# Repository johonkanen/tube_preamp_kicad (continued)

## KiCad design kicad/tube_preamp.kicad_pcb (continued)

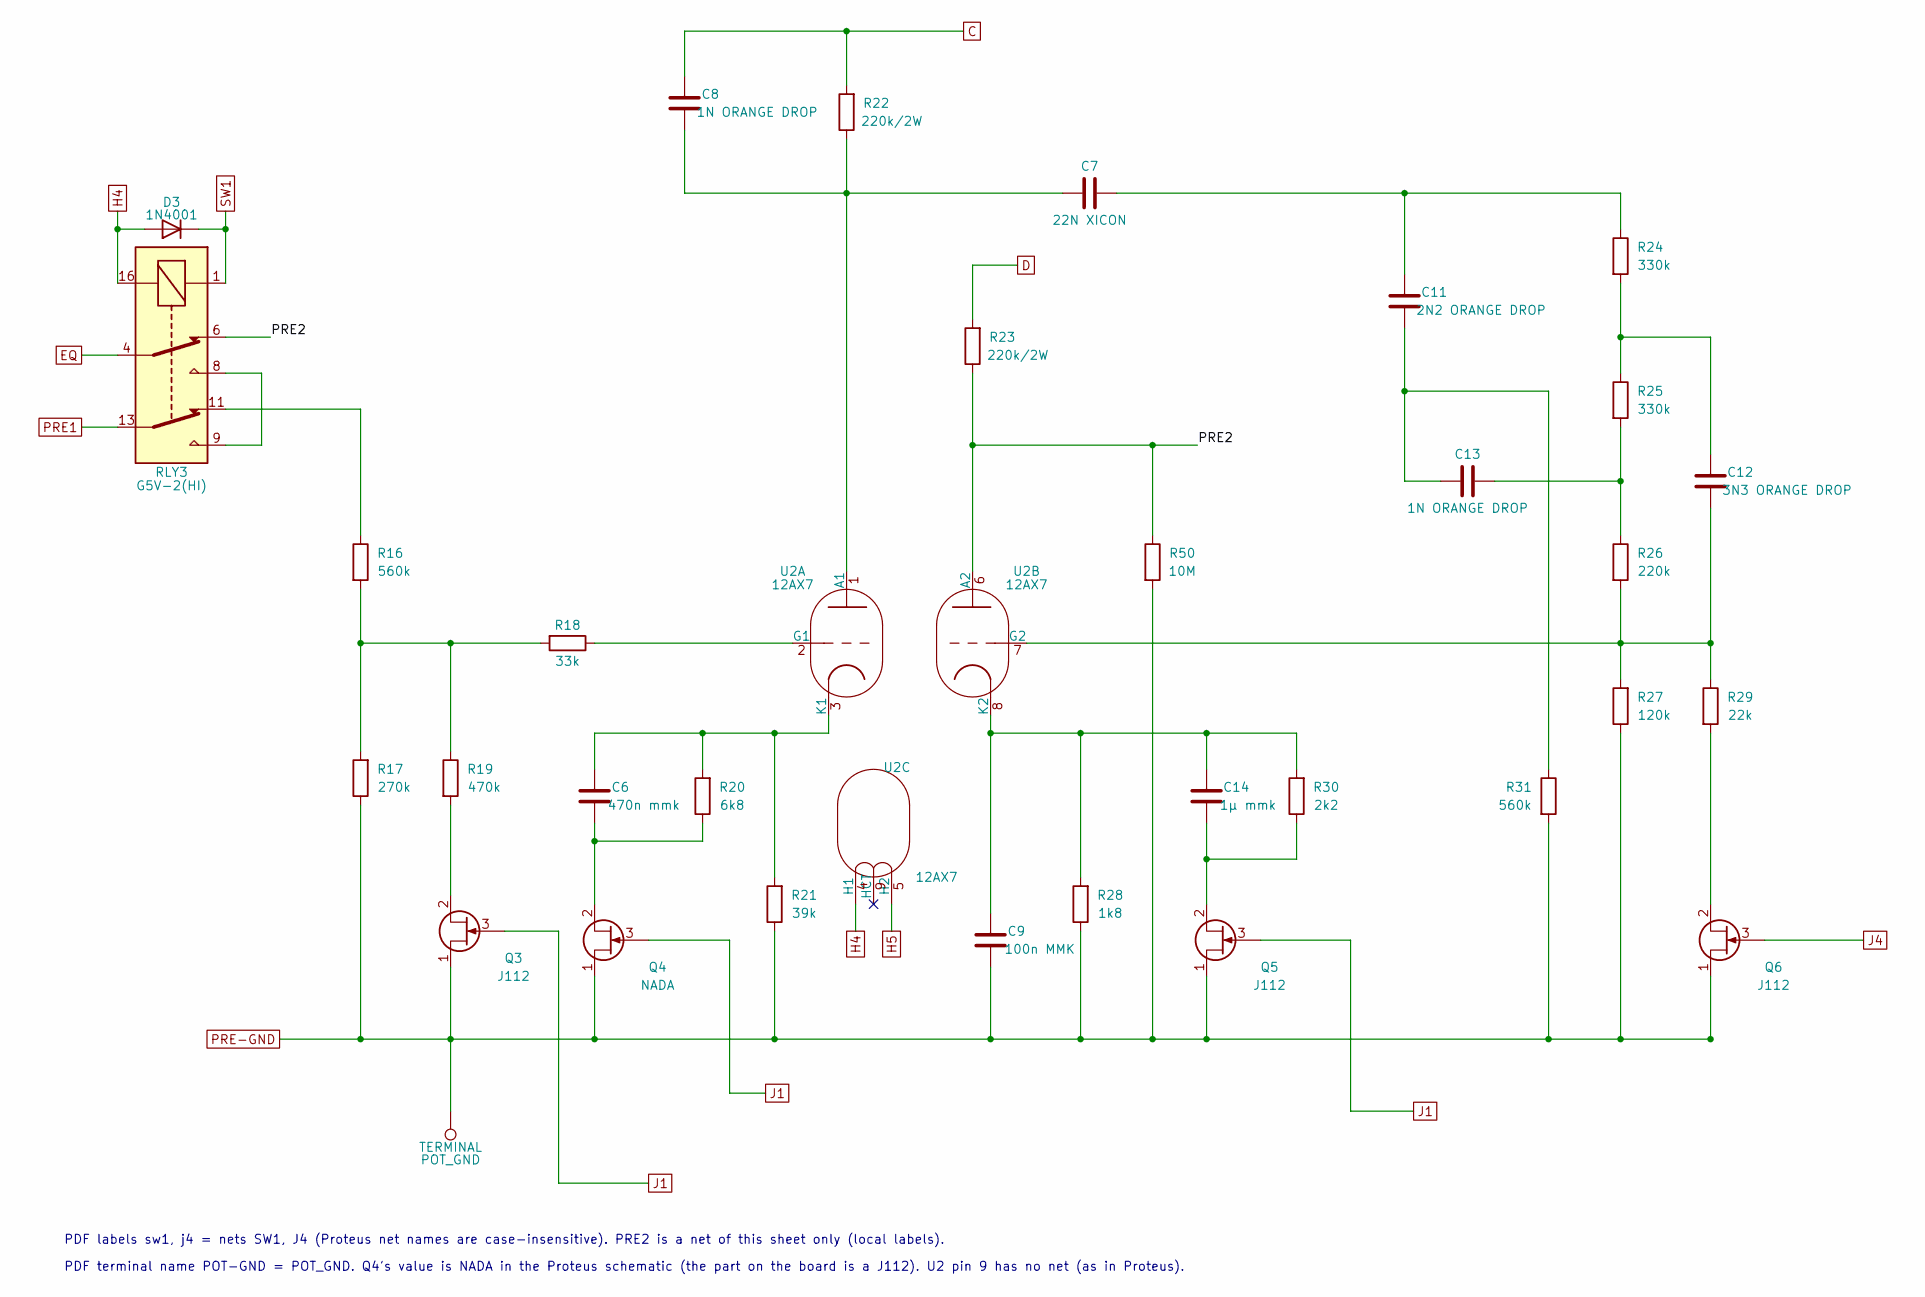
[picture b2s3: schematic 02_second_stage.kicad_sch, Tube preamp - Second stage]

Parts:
C6: 470n mmk; C_Rect_L7.2mm_W2.5mm_P5.00mm_FKS2_FKP2_MKS2_MKP2
C7: 22N XICON; C_Rect_L13.0mm_W6.0mm_P9.70mm
C8, C13: 1N ORANGE DROP; C_Rect_L16.5mm_W7.0mm_P9.70mm
C9: 100n MMK; C_Rect_L7.2mm_W2.5mm_P5.00mm_FKS2_FKP2_MKS2_MKP2
C11: 2N2 ORANGE DROP; C_Rect_L16.5mm_W7.0mm_P9.70mm
C12: 3N3 ORANGE DROP; C_Rect_L16.5mm_W7.0mm_P9.70mm
C14: 1µ mmk; C_Rect_L7.2mm_W5.0mm_P5.00mm
D3: 1N4001; D_DO-41_SOD81_P10.16mm_Horizontal_AK
POT_GND: TERMINAL; FlyLead_Pad_D3.048mm_Drill1.524mm
Q3, Q5, Q6: J112; TO-92_Inline_P2.03mm
Q4: NADA; TO-92_Inline_P2.03mm
R16, R31: 560k; R_Axial_DIN0207_L6.3mm_D2.5mm_P10.16mm_Horizontal
R17: 270k; R_Axial_DIN0207_L6.3mm_D2.5mm_P10.16mm_Horizontal
R18: 33k; R_Axial_DIN0207_L6.3mm_D2.5mm_P10.16mm_Horizontal
R19: 470k; R_Axial_DIN0207_L6.3mm_D2.5mm_P10.16mm_Horizontal
R20: 6k8; R_Axial_DIN0207_L6.3mm_D2.5mm_P10.16mm_Horizontal
R21: 39k; R_Axial_DIN0207_L6.3mm_D2.5mm_P10.16mm_Horizontal
R22, R23: 220k/2W; R_Axial_DIN0414_L11.9mm_D4.5mm_P19.05mm_Horizontal
R24, R25: 330k; R_Axial_DIN0207_L6.3mm_D2.5mm_P10.16mm_Horizontal
R26: 220k; R_Axial_DIN0207_L6.3mm_D2.5mm_P10.16mm_Horizontal
R27: 120k; R_Axial_DIN0207_L6.3mm_D2.5mm_P10.16mm_Horizontal
R28: 1k8; R_Axial_DIN0207_L6.3mm_D2.5mm_P10.16mm_Horizontal
R29: 22k; R_Axial_DIN0207_L6.3mm_D2.5mm_P10.16mm_Horizontal
R30: 2k2; R_Axial_DIN0207_L6.3mm_D2.5mm_P10.16mm_Horizontal
R50: 10M; R_Axial_DIN0207_L6.3mm_D2.5mm_P10.16mm_Horizontal
RLY3: G5V-2(HI); Relay_DPDT_Omron_G5V-2
U2: 12AX7; Valve_Noval_Belton_PCD21.00mm

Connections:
/02 Second stage/PRE2: R23.1, R50.1, RLY3.6, U2.6 (A2)
C: C8.1, R22.2; also elsewhere on the board
D: R23.2; also elsewhere on the board
EQ: RLY3.4; also elsewhere on the board
H4: D3.A, RLY3.16, U2.4 (H1); also elsewhere on the board
H5: U2.5 (H2); also elsewhere on the board
J1: Q3.3 (G), Q4.3 (G), Q5.3 (G); also elsewhere on the board
J4: Q6.3 (G); also elsewhere on the board
unnamed: C11.1, C13.2, R31.1
unnamed: C7.2, C11.2, R24.1
unnamed: C12.2, R24.2, R25.1
unnamed: C13.1, R25.2, R26.1
unnamed: Q3.2 (S), R19.2
unnamed: C6.1, Q4.2 (S), R20.1
unnamed: C14.1, Q5.2 (S), R30.1
unnamed: Q6.2 (S), R29.2
unnamed: R16.1, RLY3.11
unnamed: R16.2, R17.2, R18.2, R19.1
unnamed: RLY3.8, RLY3.9
unnamed: C7.1, C8.2, R22.1, U2.1 (A1)
unnamed: R18.1, U2.2 (G1)
unnamed: C6.2, R20.2, R21.2, U2.3 (K1)
unnamed: C12.1, R26.2, R27.2, R29.1, U2.7 (G2)
unnamed: C9.2, C14.2, R28.2, R30.2, U2.8 (K2)
PRE1: RLY3.13; also elsewhere on the board
PRE-GND: C9.1, POT_GND.1, Q3.1 (D), Q4.1 (D), Q5.1 (D), Q6.1 (D), R17.1, R21.1, R27.1, R28.1, R31.2, R50.2; also elsewhere on the board
SW1: D3.K, RLY3.1; also elsewhere on the board

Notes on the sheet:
PDF labels sw1, j4 = nets SW1, J4 (Proteus net names are case-insensitive). PRE2 is a net of this sheet only (local labels).
PDF terminal name POT-GND = POT_GND. Q4's value is NADA in the Proteus schematic (the part on the board is a J112). U2 pin 9 has no net (as in Proteus).

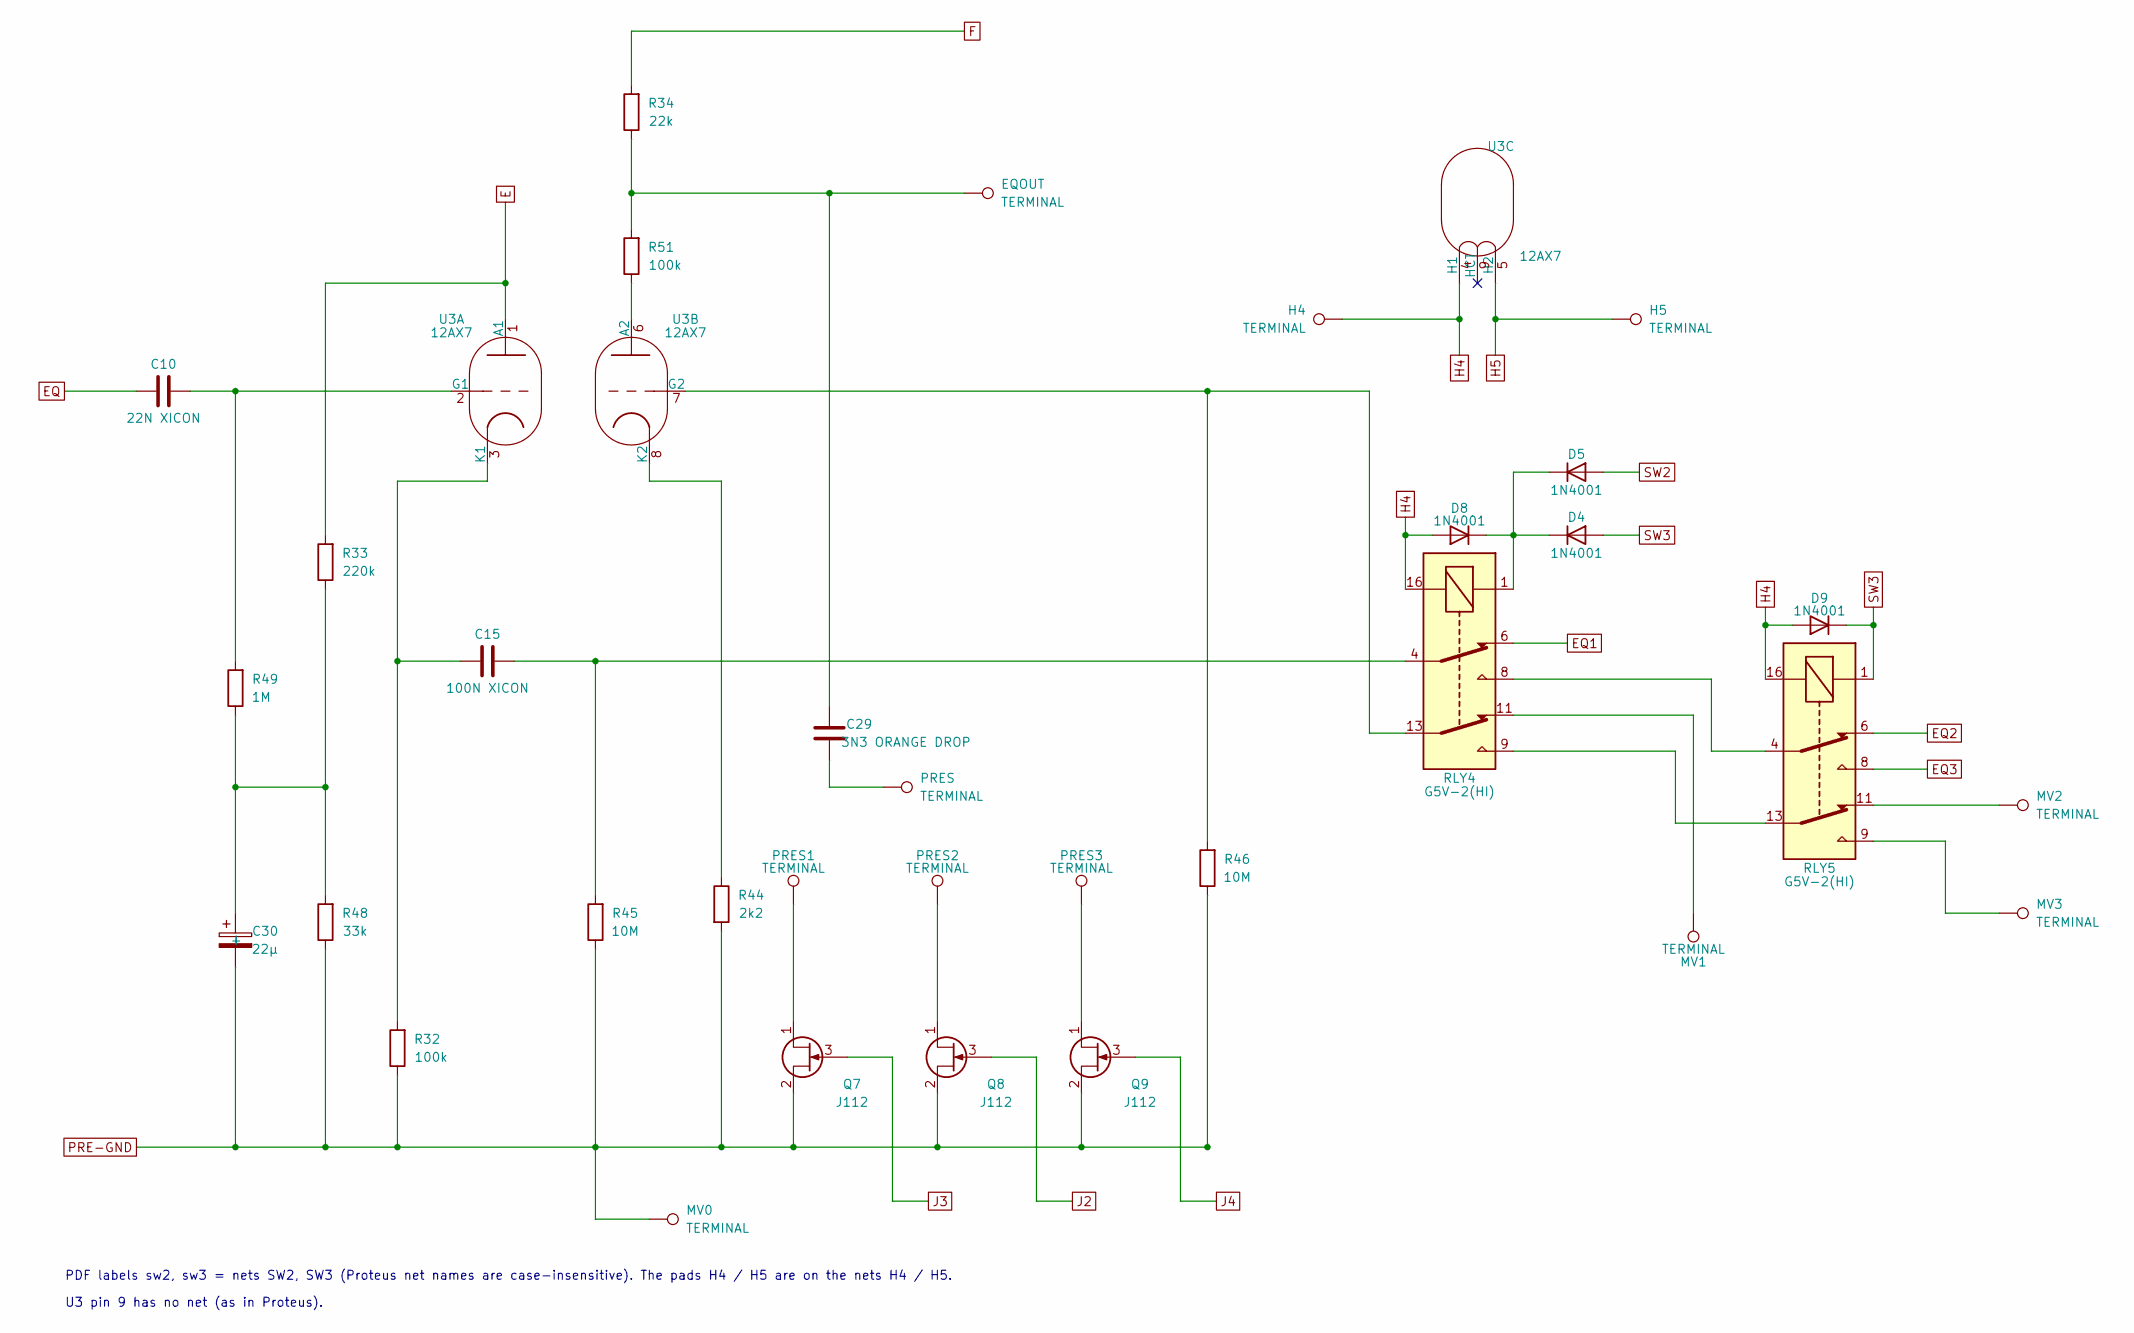
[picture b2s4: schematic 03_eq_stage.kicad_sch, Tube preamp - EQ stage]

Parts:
C10: 22N XICON; C_Rect_L13.0mm_W6.0mm_P9.70mm
C15: 100N XICON; C_Rect_L24.0mm_W7.0mm_P20.00mm
C29: 3N3 ORANGE DROP; C_Rect_L16.5mm_W7.0mm_P9.70mm
C30: 22µ; CP_Radial_D6.3mm_P2.50mm_PM
D4, D5, D8, D9: 1N4001; D_DO-41_SOD81_P10.16mm_Horizontal_AK
EQOUT: TERMINAL; FlyLead_Pad_D3.048mm_Drill1.524mm
H4, H5: TERMINAL; FlyLead_Pad_D3.048mm_Drill1.524mm
MV0, MV1, MV2, MV3: TERMINAL; FlyLead_Pad_D3.048mm_Drill1.524mm
PRES, PRES1, PRES2, PRES3: TERMINAL; FlyLead_Pad_D3.048mm_Drill1.524mm
Q7, Q8, Q9: J112; TO-92_Inline_P2.03mm
R32, R51: 100k; R_Axial_DIN0207_L6.3mm_D2.5mm_P10.16mm_Horizontal
R33: 220k; R_Axial_DIN0414_L11.9mm_D4.5mm_P19.05mm_Horizontal
R34: 22k; R_Axial_DIN0207_L6.3mm_D2.5mm_P10.16mm_Horizontal
R44: 2k2; R_Axial_DIN0207_L6.3mm_D2.5mm_P10.16mm_Horizontal
R45, R46: 10M; R_Axial_DIN0207_L6.3mm_D2.5mm_P10.16mm_Horizontal
R48: 33k; R_Axial_DIN0207_L6.3mm_D2.5mm_P10.16mm_Horizontal
R49: 1M; R_Axial_DIN0207_L6.3mm_D2.5mm_P10.16mm_Horizontal
RLY4, RLY5: G5V-2(HI); Relay_DPDT_Omron_G5V-2
U3: 12AX7; Valve_Noval_Belton_PCD21.00mm

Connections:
E: R33.2, U3.1 (A1); also elsewhere on the board
EQ: C10.1; also elsewhere on the board
EQ1: RLY4.6; also elsewhere on the board
EQ2: RLY5.6; also elsewhere on the board
EQ3: RLY5.8; also elsewhere on the board
F: R34.2; also elsewhere on the board
H4: D8.A, D9.A, H4.1, RLY4.16, RLY5.16, U3.4 (H1); also elsewhere on the board
H5: H5.1, U3.5 (H2); also elsewhere on the board
J2: Q8.3 (G); also elsewhere on the board
J3: Q7.3 (G); also elsewhere on the board
J4: Q9.3 (G); also elsewhere on the board
unnamed: C15.2, R45.2, RLY4.4
unnamed: C29.1, EQOUT.1, R34.1, R51.2
unnamed: C29.2, PRES.1
unnamed: C30.+, R33.1, R48.2, R49.1
unnamed: D4.K, D5.K, D8.K, RLY4.1
unnamed: MV1.1, RLY4.11
unnamed: MV2.1, RLY5.11
unnamed: MV3.1, RLY5.9
unnamed: PRES1.1, Q7.1 (D)
unnamed: PRES2.1, Q8.1 (D)
unnamed: PRES3.1, Q9.1 (D)
unnamed: RLY4.8, RLY5.4
unnamed: RLY4.9, RLY5.13
unnamed: C10.2, R49.2, U3.2 (G1)
unnamed: C15.1, R32.2, U3.3 (K1)
unnamed: R51.1, U3.6 (A2)
unnamed: R46.2, RLY4.13, U3.7 (G2)
unnamed: R44.1, U3.8 (K2)
PRE-GND: C30.-, MV0.1, Q7.2 (S), Q8.2 (S), Q9.2 (S), R32.1, R44.2, R45.1, R46.1, R48.1; also elsewhere on the board
SW2: D5.A; also elsewhere on the board
SW3: D4.A, D9.K, RLY5.1; also elsewhere on the board

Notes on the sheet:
PDF labels sw2, sw3 = nets SW2, SW3 (Proteus net names are case-insensitive). The pads H4 / H5 are on the nets H4 / H5.
U3 pin 9 has no net (as in Proteus).

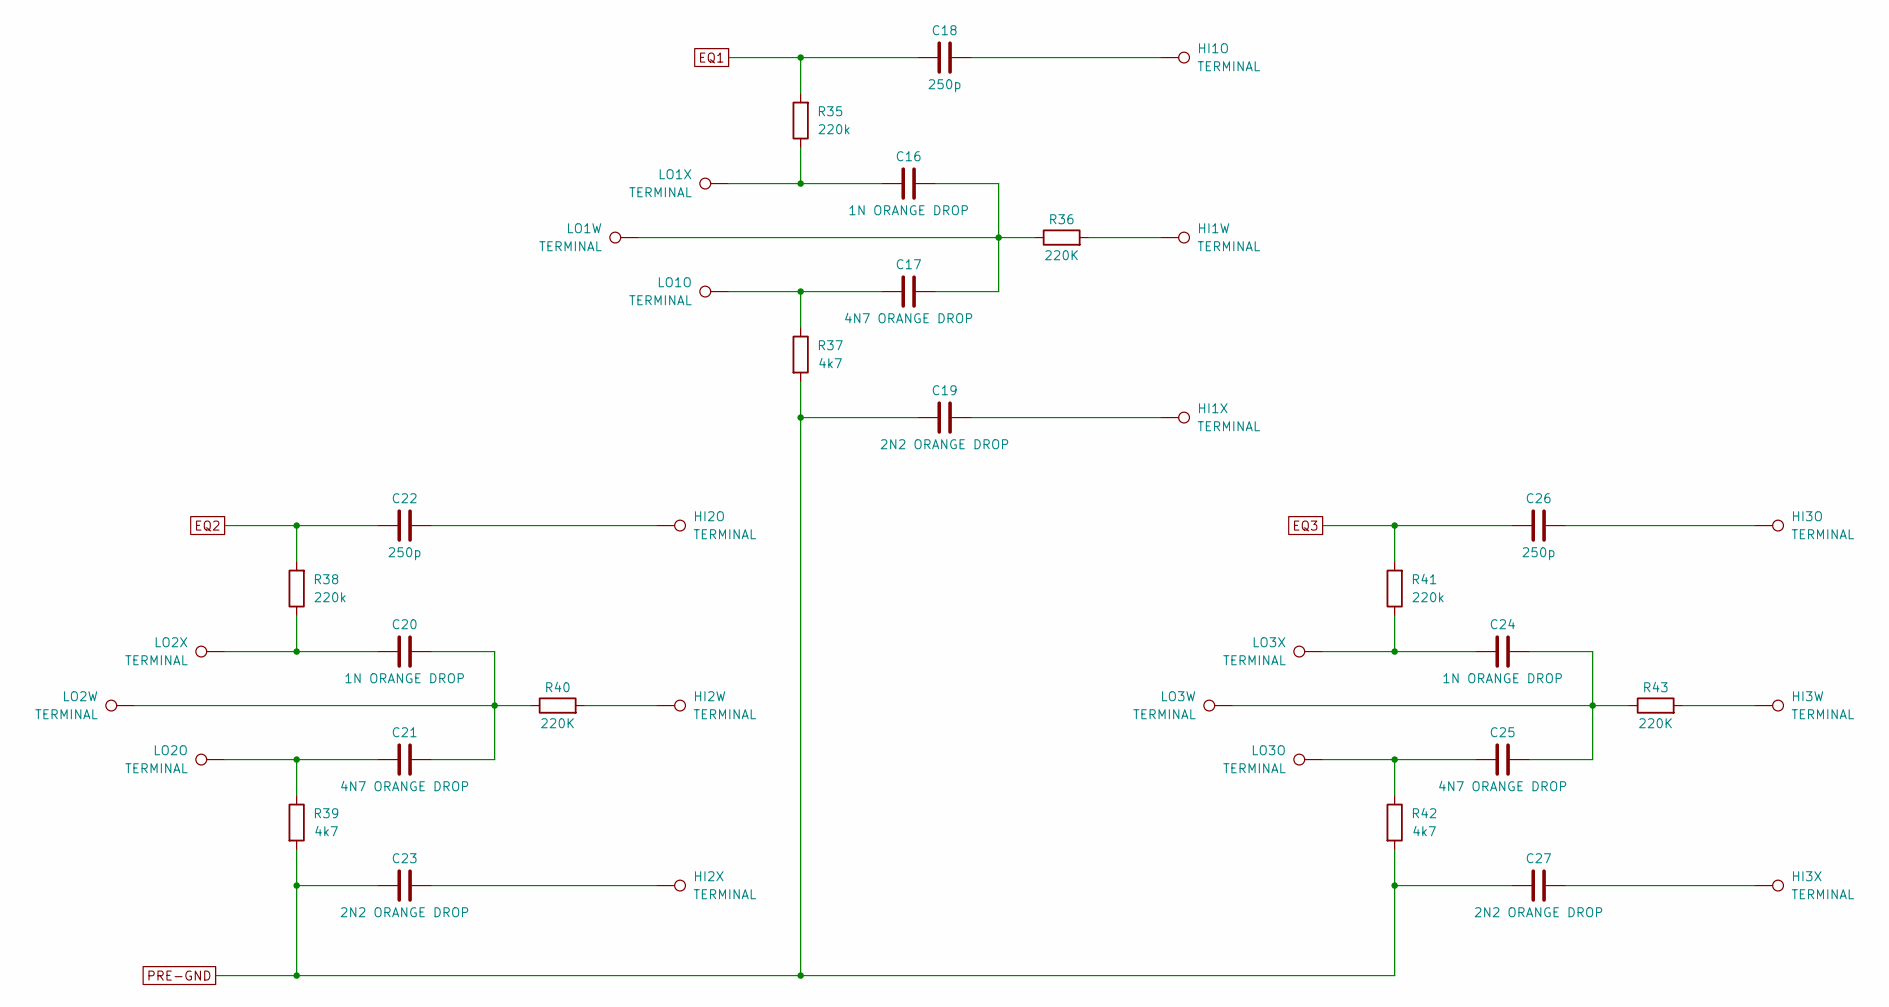
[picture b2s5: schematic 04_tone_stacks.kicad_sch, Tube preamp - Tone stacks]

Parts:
C16, C20, C24: 1N ORANGE DROP; C_Rect_L16.5mm_W7.0mm_P9.70mm
C17, C21, C25: 4N7 ORANGE DROP; C_Rect_L16.5mm_W7.0mm_P9.70mm
C18, C22, C26: 250p; C_Disc_D7.5mm_W2.5mm_P5.08mm
C19, C23, C27: 2N2 ORANGE DROP; C_Rect_L16.5mm_W7.0mm_P9.70mm
HI1O, HI1W, HI1X, HI2O, HI2W, HI2X, HI3O, HI3W, HI3X: TERMINAL; FlyLead_Pad_D3.048mm_Drill1.524mm
LO1O, LO1W, LO1X, LO2O, LO2W, LO2X, LO3O, LO3W, LO3X: TERMINAL; FlyLead_Pad_D3.048mm_Drill1.524mm
R35, R38, R41: 220k; R_Axial_DIN0207_L6.3mm_D2.5mm_P10.16mm_Horizontal
R36, R40, R43: 220K; R_Axial_DIN0207_L6.3mm_D2.5mm_P10.16mm_Horizontal
R37, R39, R42: 4k7; R_Axial_DIN0207_L6.3mm_D2.5mm_P10.16mm_Horizontal

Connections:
EQ1: C18.1, R35.2; also elsewhere on the board
EQ2: C22.1, R38.2; also elsewhere on the board
EQ3: C26.1, R41.2; also elsewhere on the board
unnamed: C16.1, LO1X.1, R35.1
unnamed: C16.2, C17.2, LO1W.1, R36.1
unnamed: C17.1, LO1O.1, R37.1
unnamed: C18.2, HI1O.1
unnamed: C19.2, HI1X.1
unnamed: C20.1, LO2X.1, R38.1
unnamed: C20.2, C21.2, LO2W.1, R40.1
unnamed: C21.1, LO2O.1, R39.1
unnamed: C22.2, HI2O.1
unnamed: C23.2, HI2X.1
unnamed: C24.1, LO3X.1, R41.1
unnamed: C24.2, C25.2, LO3W.1, R43.1
unnamed: C25.1, LO3O.1, R42.1
unnamed: C26.2, HI3O.1
unnamed: C27.2, HI3X.1
unnamed: HI1W.1, R36.2
unnamed: HI2W.1, R40.2
unnamed: HI3W.1, R43.2
PRE-GND: C19.1, C23.1, C27.1, R37.2, R39.2, R42.2; also elsewhere on the board

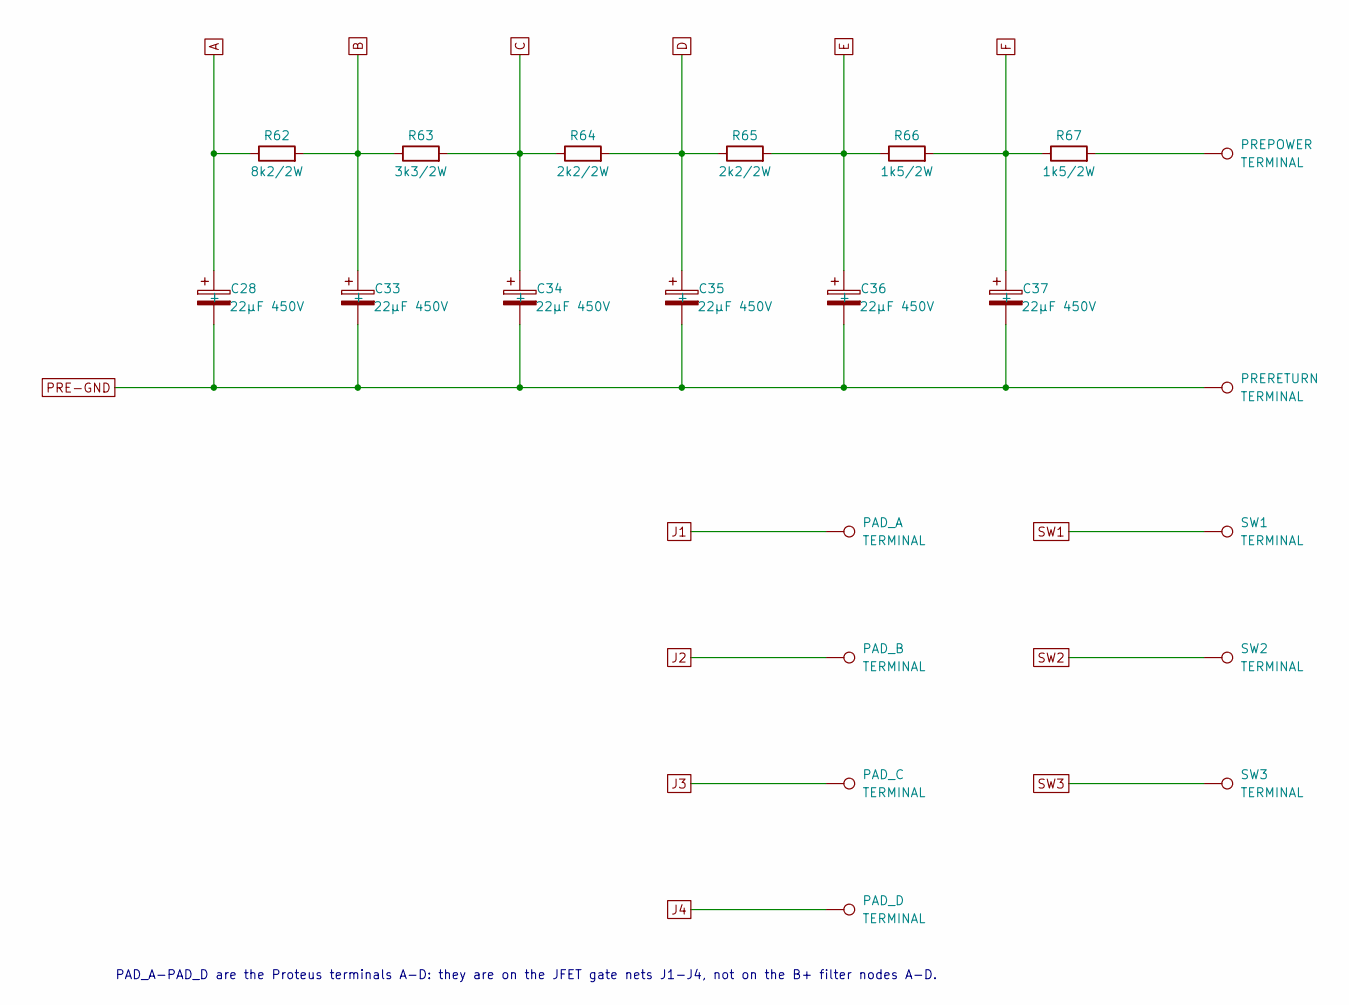
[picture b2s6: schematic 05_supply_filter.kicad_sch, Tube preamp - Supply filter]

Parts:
C28, C33, C34, C35, C36, C37: 22µF 450V; CP_Radial_D16.0mm_P7.50mm_Pin2Plus
PAD_A: TERMINAL; FlyLead_Pad_D3.048mm_Drill1.524mm
PAD_B: TERMINAL; FlyLead_Pad_D3.048mm_Drill1.524mm
PAD_C: TERMINAL; FlyLead_Pad_D3.048mm_Drill1.524mm
PAD_D: TERMINAL; FlyLead_Pad_D3.048mm_Drill1.524mm
PREPOWER: TERMINAL; FlyLead_Pad_D3.048mm_Drill1.524mm
PRERETURN: TERMINAL; FlyLead_Pad_D3.048mm_Drill1.524mm
R62: 8k2/2W; R_Axial_DIN0414_L11.9mm_D4.5mm_P19.05mm_Horizontal
R63: 3k3/2W; R_Axial_DIN0414_L11.9mm_D4.5mm_P19.05mm_Horizontal
R64, R65: 2k2/2W; R_Axial_DIN0414_L11.9mm_D4.5mm_P19.05mm_Horizontal
R66, R67: 1k5/2W; R_Axial_DIN0414_L11.9mm_D4.5mm_P19.05mm_Horizontal
SW1, SW2, SW3: TERMINAL; FlyLead_Pad_D3.048mm_Drill1.524mm

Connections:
A: C28.2 (+), R62.1; also elsewhere on the board
B: C33.2 (+), R62.2, R63.1; also elsewhere on the board
C: C34.2 (+), R63.2, R64.1; also elsewhere on the board
D: C35.2 (+), R64.2, R65.1; also elsewhere on the board
E: C36.2 (+), R65.2, R66.1; also elsewhere on the board
F: C37.2 (+), R66.2, R67.1; also elsewhere on the board
J1: PAD_A.1; also elsewhere on the board
J2: PAD_B.1; also elsewhere on the board
J3: PAD_C.1; also elsewhere on the board
J4: PAD_D.1; also elsewhere on the board
unnamed: PREPOWER.1, R67.2
PRE-GND: C28.1 (-), C33.1 (-), C34.1 (-), C35.1 (-), C36.1 (-), C37.1 (-), PRERETURN.1; also elsewhere on the board
SW1: SW1.1; also elsewhere on the board
SW2: SW2.1; also elsewhere on the board
SW3: SW3.1; also elsewhere on the board

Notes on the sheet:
PAD_A-PAD_D are the Proteus terminals A-D: they are on the JFET gate nets J1-J4, not on the B+ filter nodes A-D.

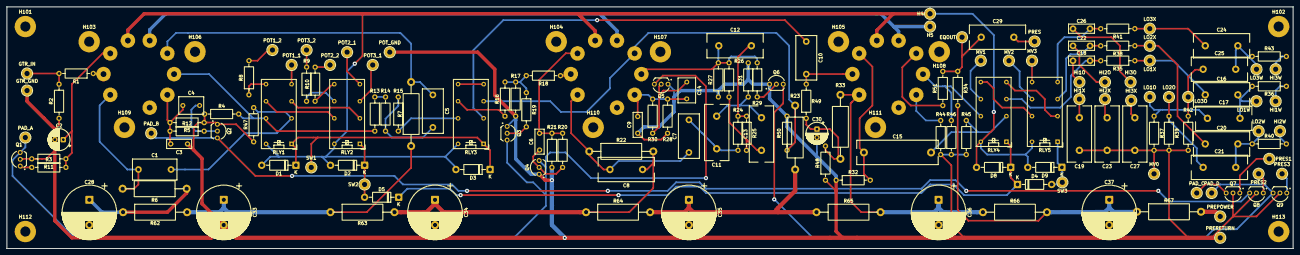
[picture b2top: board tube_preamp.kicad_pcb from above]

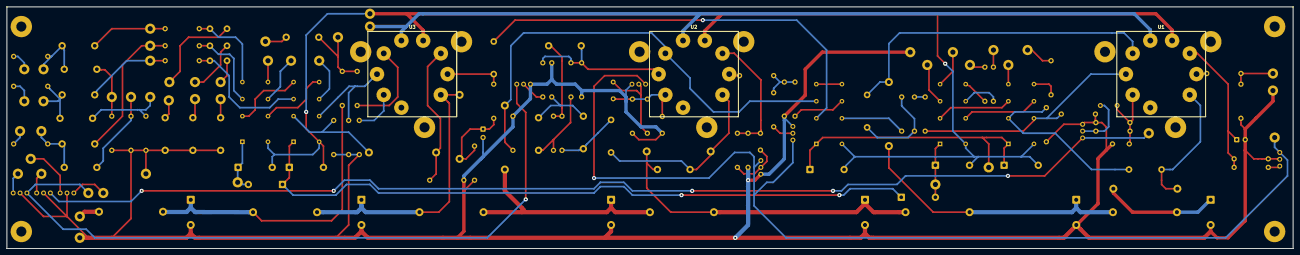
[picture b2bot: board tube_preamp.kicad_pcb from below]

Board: 2 copper layers, 382.8 x 71.9 mm, 176 parts (3 on the bottom side), 98 nets.

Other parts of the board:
H101, H102, H103, H104, H105, H106, H107, H108, H109, H110, H111, H112, H113: MountingHole_3.0mm; MountingHole_3.0mm_PTH_Pad6.35mm
